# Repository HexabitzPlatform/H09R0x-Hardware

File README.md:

# H09R0x-Hardware
Hexabitz Thermocouple Sensor Module Hardware Design

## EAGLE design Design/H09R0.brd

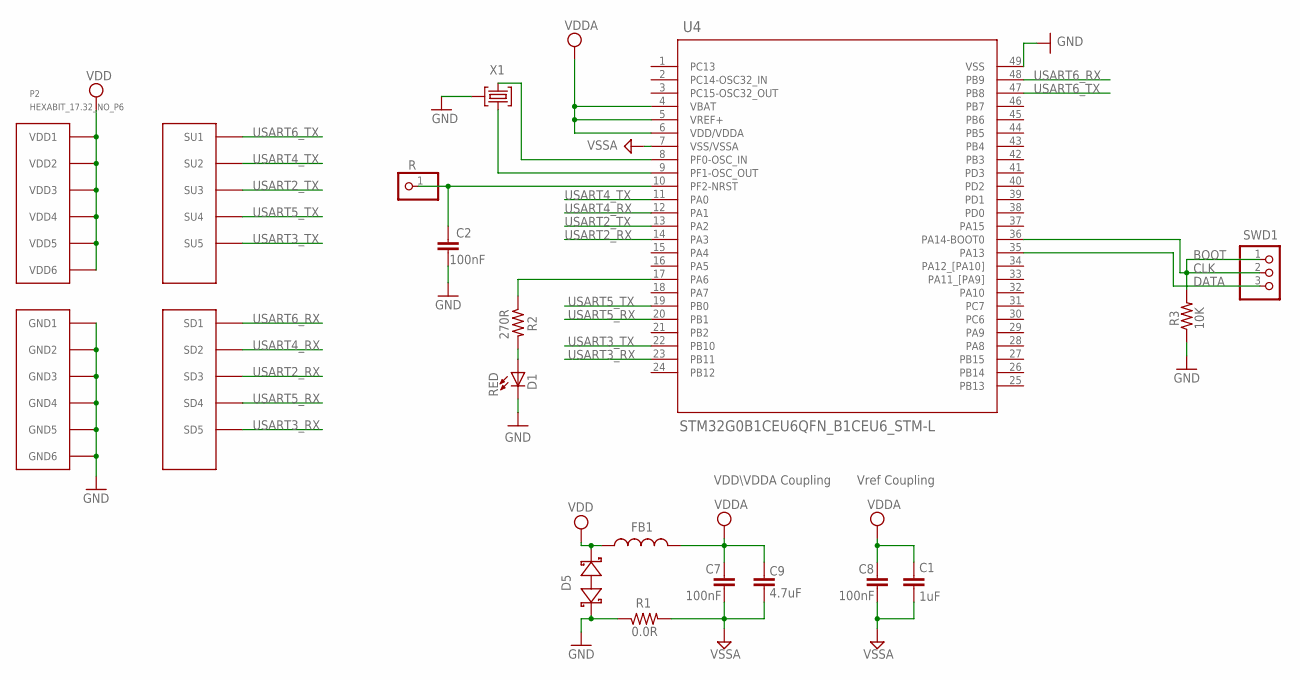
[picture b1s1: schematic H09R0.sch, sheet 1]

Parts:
C1: 1uF; C-0805
C2, C7, C8: 100nF; C-0603
C9: 4.7uF; C-0805
D1: RED; VLMS1300-GS08; MPN VLMS1300-GS08
D5: BOURNS_CDSOD323-T03SCBOURNS_CDSOD323-T03SC_0_0; BOURNS_CDSOD323-T03SC_0
FB1: FB-TDK_MMZ1608Y300B; FB-0603; MPN MMZ1608Y300B
P2: HEXABIT_17.32_NO_P6
R: R; 1X01
R1: 0.0R; R-0603; MPN RC0603JR-070RL
R2: 270R; R-0603
R3: 10K; R-0603
SWD1: PINHD-1X3; 1X03
U4: STM32G0B1CEU6QFN_B1CEU6_STM-L; QFN_B1CEU6_STM-L
X1: XTALL_CSTCE8M00G52

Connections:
CLK: R3.2, SWD1.1, SWD1.2, U4.36 (PA14-BOOT0)
DATA: SWD1.3, U4.35 (PA13)
GND: C2.2, D1.C, D5.1 (A), P2.PAD_PD7 (GND1), P2.PAD_PD8 (GND2), P2.PAD_PD9 (GND3), P2.PAD_PD10 (GND4), P2.PAD_PD11 (GND5), P2.PAD_PD12 (GND6), R1.1, R3.1, U4.49 (VSS), X1.P$2 (2); also elsewhere on the board
unnamed: U4.9 (PF1-OSC_OUT), X1.P$1 (1)
unnamed: U4.8 (PF0-OSC_IN), X1.P$3 (3)
unnamed: C2.1, R.1, U4.10 (PF2-NRST)
unnamed: R2.1, U4.17 (PA6)
unnamed: D1.A, R2.2
USART2_RX: P2.PAD_PD3 (SD3), U4.14 (PA3)
USART2_TX: P2.PAD_PU3 (SU3), U4.13 (PA2)
USART3_RX: P2.PAD_PD5 (SD5), U4.23 (PB11)
USART3_TX: P2.PAD_PU5 (SU5), U4.22 (PB10)
USART4_RX: P2.PAD_PD2 (SD2), U4.12 (PA1)
USART4_TX: P2.PAD_PU2 (SU2), U4.11 (PA0)
USART5_RX: P2.PAD_PD4 (SD4), U4.20 (PB1)
USART5_TX: P2.PAD_PU4 (SU4), U4.19 (PB0)
USART6_RX: P2.PAD_PD1 (SD1), U4.48 (PB9)
USART6_TX: P2.PAD_PU1 (SU1), U4.47 (PB8)
VDD: D5.2 (C), FB1.2, P2.PAD_PU7 (VDD1), P2.PAD_PU8 (VDD2), P2.PAD_PU9 (VDD3), P2.PAD_PU10 (VDD4), P2.PAD_PU11 (VDD5), P2.PAD_PU12 (VDD6); also elsewhere on the board
VDDA: C1.1, C7.1, C8.1, C9.1, FB1.1, U4.4 (VBAT), U4.5 (VREF+), U4.6 (VDD/VDDA)
VSSA: C1.2, C7.2, C8.2, C9.2, R1.2, U4.7 (VSS/VSSA)

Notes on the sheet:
Vref Coupling
VDD\VDDA Coupling
BOOT

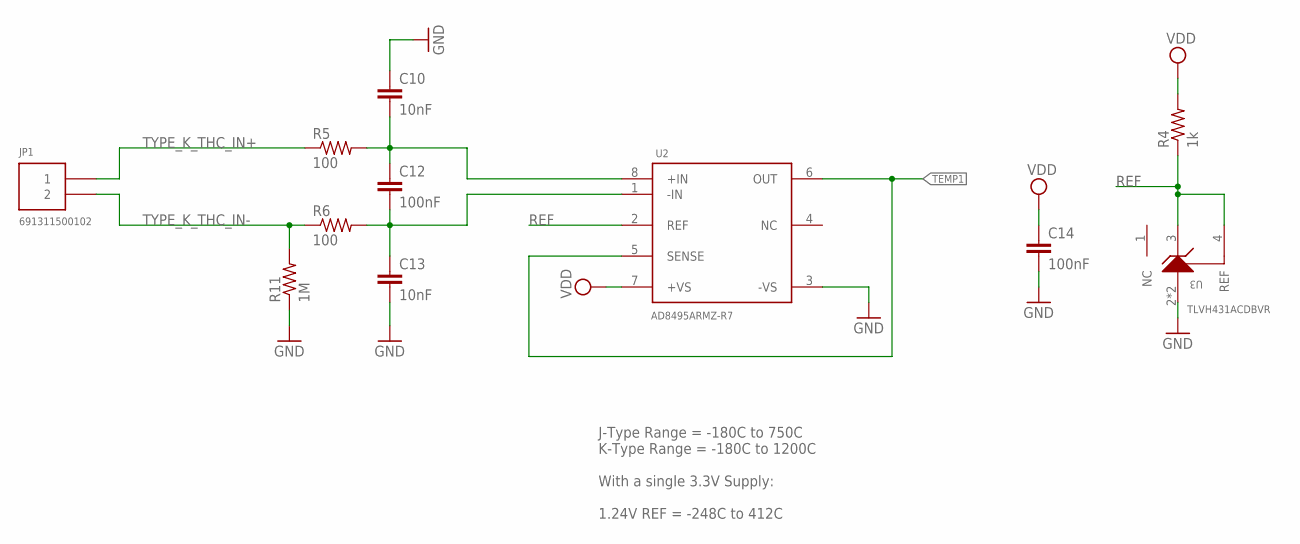
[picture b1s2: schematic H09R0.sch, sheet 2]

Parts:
C10, C13: 10nF; C-0603; TOLERANCE 10%; VOLTAGE_RATING 50V; MPN C0603C103K5RACTU
C12, C14: 100nF; C-0603; TOLERANCE 10%; VOLTAGE_RATING 10V; MPN C0603C104K8RACTU
JP1: 691311500102; 1546111-2
R4: 1k; R-0402; TOLERANCE 1%; MPN RC0402FR-071KL
R5, R6: 100; R-0402; TOLERANCE 1%; MPN RC0402FR-07100RL
R11: 1M; R-0402; TOLERANCE 1%; MPN RC0402FR-071ML
U2: AD8495ARMZ-R7; AD8495ARMZ
U3: TLVH431ACDBVR

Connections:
GND: C10.1, C13.2, C14.2, R11.1, U2.3 (-VS), U3.2 (ANODE), U3.5 (ANODE); also elsewhere on the board
unnamed: C10.2, C12.1, R5.2, U2.8 (+IN)
unnamed: C12.2, C13.1, R6.2, U2.1 (-IN)
REF: R4.1, U2.2 (REF), U3.3 (CATHODE), U3.4 (REF)
TEMP1: U2.5 (SENSE), U2.6 (OUT)
TYPE_K_THC_IN+: JP1.1, R5.1
TYPE_K_THC_IN-: JP1.2, R6.1, R11.2
VDD: C14.1, R4.2, U2.7 (+VS); also elsewhere on the board

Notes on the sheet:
J-Type Range = -180C to 750C K-Type Range = -180C to 1200C With a single 3.3V Supply: 1.24V REF = -248C to 412C

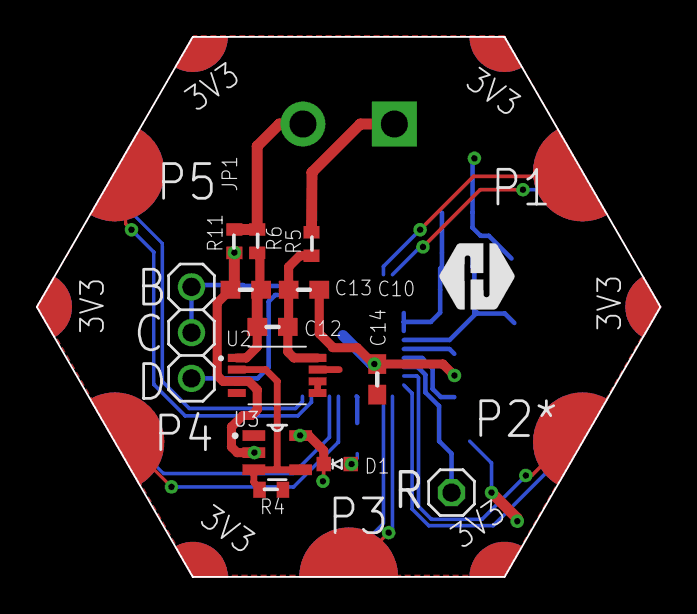
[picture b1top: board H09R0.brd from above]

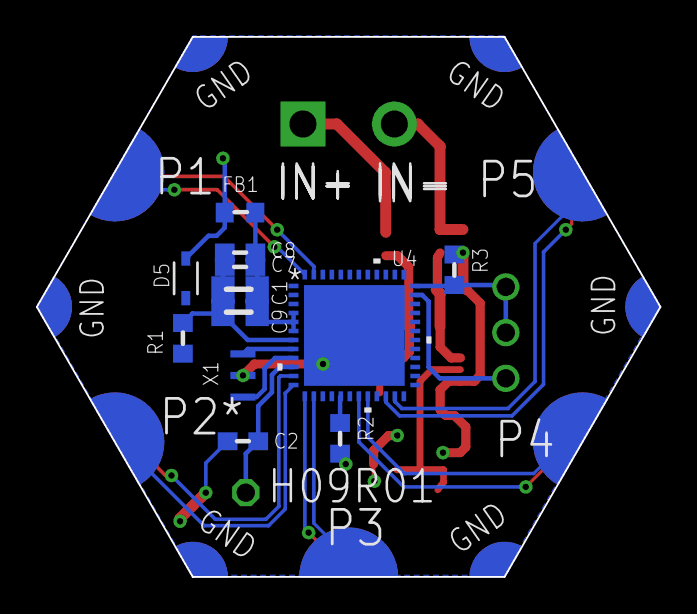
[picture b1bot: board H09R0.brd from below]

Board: 2 copper layers, 34.6 x 30.0 mm, 28 parts (12 on the bottom side), 27 nets.

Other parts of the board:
U$1: HEXA-LOGO

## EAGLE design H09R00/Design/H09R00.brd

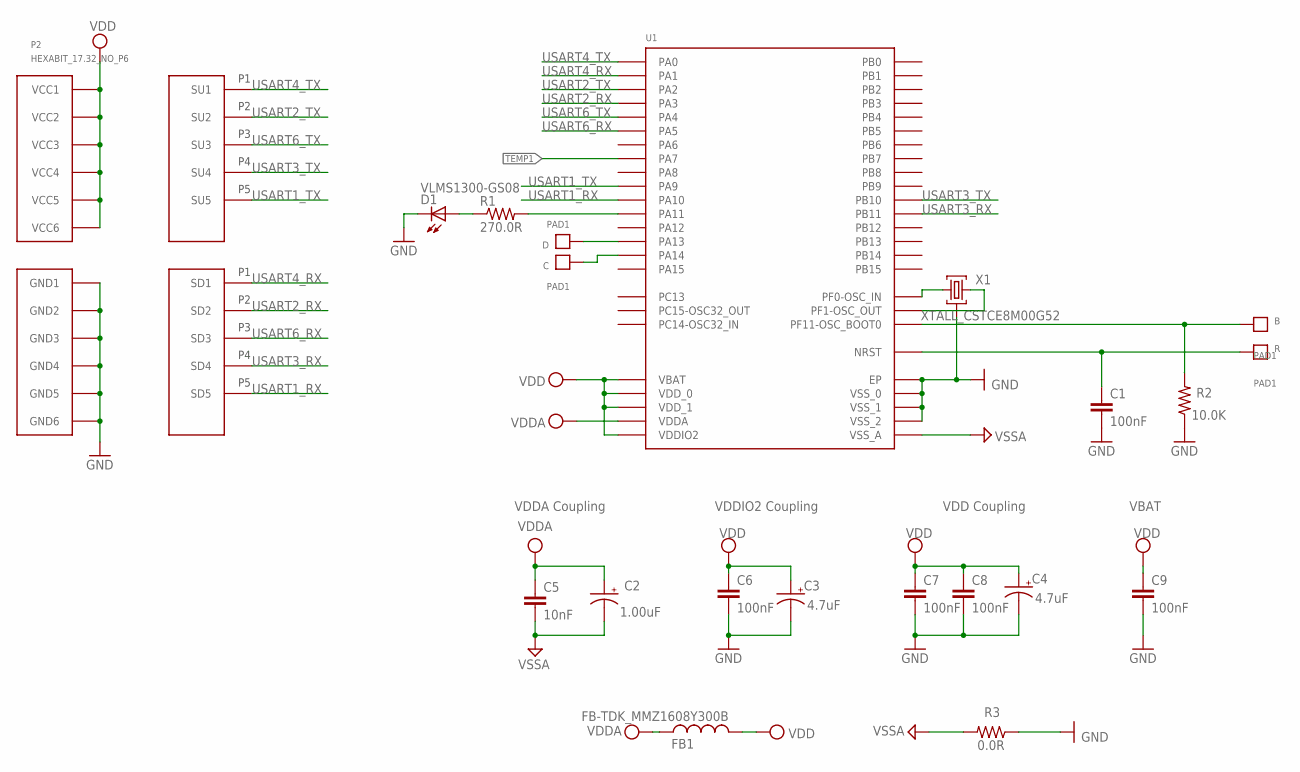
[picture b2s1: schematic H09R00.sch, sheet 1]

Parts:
B: PAD1
C: PAD1
C1, C6, C8: 100nF; C-0603; TOLERANCE 10%; VOLTAGE_RATING 10V; MPN C0603C104K8RACTU
C2: 1.00uF; C-0805-POL; TOLERANCE 10%; VOLTAGE_RATING 16V; MPN CC0805KKX7R7BB105
C3, C4: 4.7uF; C-0805-POL; TOLERANCE 10%; VOLTAGE_RATING 25V; MPN GRM21BC81E475KA12L
C5: 10nF; C-0603; TOLERANCE 10%; VOLTAGE_RATING 50V; MPN C0603C103K5RACTU
C7: 100nF; C-0603; TOLERANCE 10%; VOLTAGE_RATING 10; MPN C0603C104K8RACTU
C9: 100nF; C-0603; TOLERANCE 10V; VOLTAGE_RATING 10%; MPN C0603C104K8RACTU
D: PAD1
D1: VLMS1300-GS08; MPN VLMS1300-GS08
FB1: FB-TDK_MMZ1608Y300B; MPN MMZ1608Y300B
P2: HEXABIT_17.32_NO_P6
R: PAD1
R1: 270.0R; R-0603; TOLERANCE 1%; MPN RC0603FR-07270RL
R2: 10.0K; R-0603; TOLERANCE 5%; MPN RC0603JR-0710KL
R3: 0.0R; R-0603; MPN RC0603JR-070RL
U1: STM32F091CBU6
X1: XTALL_CSTCE8M00G52

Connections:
B: B.P$1, B.P$2, R2.2, U1.P$44 (PF11-OSC_BOOT0)
GND: C1.2, C3.2 (-), C4.2 (-), C6.2, C7.2, C8.2, C9.2, D1.C, P2.7 (GND1), P2.8 (GND2), P2.9 (GND3), P2.10 (GND4), P2.11 (GND5), P2.12 (GND6), R2.1, R3.1, U1.EP, U1.P$23 (VSS_0), U1.P$35 (VSS_1), U1.P$47 (VSS_2), X1.P$2 (2); also elsewhere on the board
unnamed: D.P$1, D.P$2, U1.P$34 (PA13)
unnamed: C.P$1, C.P$2, U1.P$37 (PA14)
unnamed: R1.2, U1.P$32 (PA11)
unnamed: D1.A, R1.1
unnamed: U1.P$5 (PF0-OSC_IN), X1.P$1 (1)
unnamed: U1.P$6 (PF1-OSC_OUT), X1.P$3 (3)
R: C1.1, R.P$1, R.P$2, U1.P$7 (NRST)
TEMP1: U1.P$17 (PA7); also elsewhere on the board
USART1_RX: P2.23 (SD5), U1.P$31 (PA10)
USART1_TX: P2.17 (SU5), U1.P$30 (PA9)
USART2_RX: P2.20 (SD2), U1.P$13 (PA3)
USART2_TX: P2.14 (SU2), U1.P$12 (PA2)
USART3_RX: P2.22 (SD4), U1.P$22 (PB11)
USART3_TX: P2.16 (SU4), U1.P$21 (PB10)
USART4_RX: P2.19 (SD1), U1.P$11 (PA1)
USART4_TX: P2.13 (SU1), U1.P$10 (PA0)
USART6_RX: P2.21 (SD3), U1.P$15 (PA5)
USART6_TX: P2.15 (SU3), U1.P$14 (PA4)
VDD: C3.1 (+), C4.1 (+), C6.1, C7.1, C8.1, C9.1, FB1.2, P2.1 (VCC1), P2.2 (VCC2), P2.3 (VCC3), P2.4 (VCC4), P2.5 (VCC5), P2.6 (VCC6), U1.P$1 (VBAT), U1.P$24 (VDD_0), U1.P$36 (VDDIO2), U1.P$48 (VDD_1); also elsewhere on the board
VDDA: C2.1 (+), C5.1, FB1.1, U1.P$9 (VDDA)
VSSA: C2.2 (-), C5.2, R3.2, U1.P$8 (VSS_A)

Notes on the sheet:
VDDA Coupling
VDDIO2 Coupling
VDD Coupling
VBAT

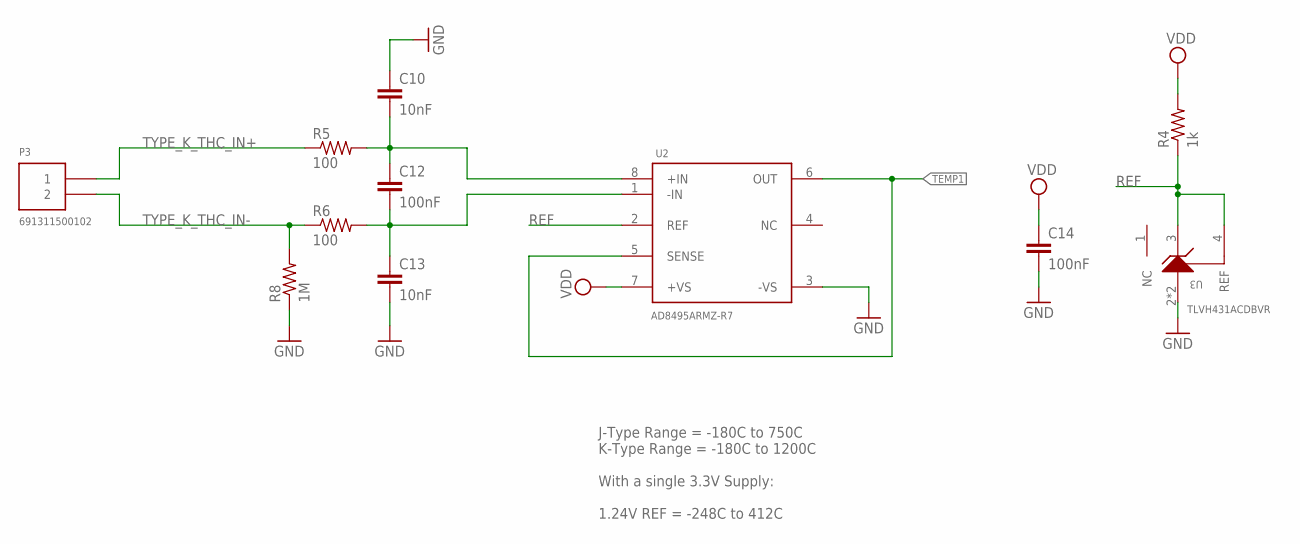
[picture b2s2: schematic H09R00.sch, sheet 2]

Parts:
C10, C13: 10nF; C-0603; TOLERANCE 10%; VOLTAGE_RATING 50V; MPN C0603C103K5RACTU
C12, C14: 100nF; C-0603; TOLERANCE 10%; VOLTAGE_RATING 10V; MPN C0603C104K8RACTU
P3: 691311500102
R4: 1k; R-0402; TOLERANCE 1%; MPN RC0402FR-071KL
R5, R6: 100; R-0402; TOLERANCE 1%; MPN RC0402FR-07100RL
R8: 1M; R-0402; TOLERANCE 1%; MPN RC0402FR-071ML
U2: AD8495ARMZ-R7; AD8495ARMZ
U3: TLVH431ACDBVR

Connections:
GND: C10.1, C13.2, C14.2, R8.1, U2.3 (-VS), U3.2 (ANODE), U3.5 (ANODE); also elsewhere on the board
unnamed: C10.2, C12.1, R5.2, U2.8 (+IN)
unnamed: C12.2, C13.1, R6.2, U2.1 (-IN)
REF: R4.1, U2.2 (REF), U3.3 (CATHODE), U3.4 (REF)
TEMP1: U2.5 (SENSE), U2.6 (OUT); also elsewhere on the board
TYPE_K_THC_IN+: P3.1, R5.1
TYPE_K_THC_IN-: P3.2, R6.1, R8.2
VDD: C14.1, R4.2, U2.7 (+VS); also elsewhere on the board

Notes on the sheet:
J-Type Range = -180C to 750C K-Type Range = -180C to 1200C With a single 3.3V Supply: 1.24V REF = -248C to 412C

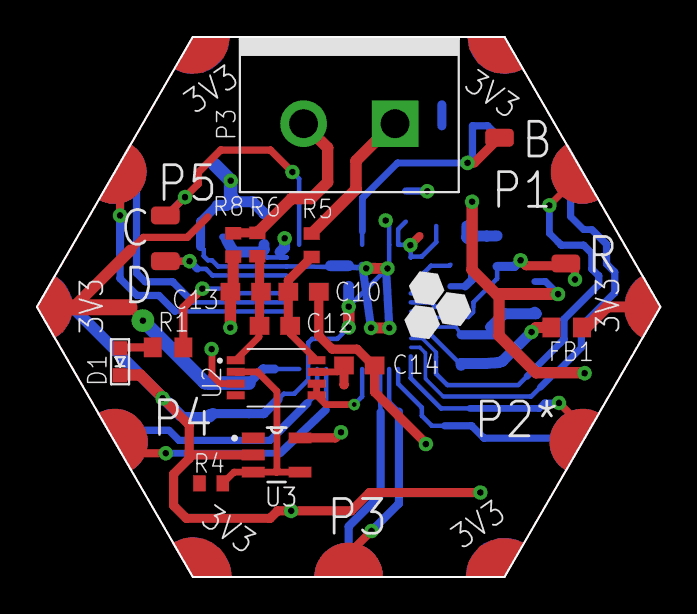
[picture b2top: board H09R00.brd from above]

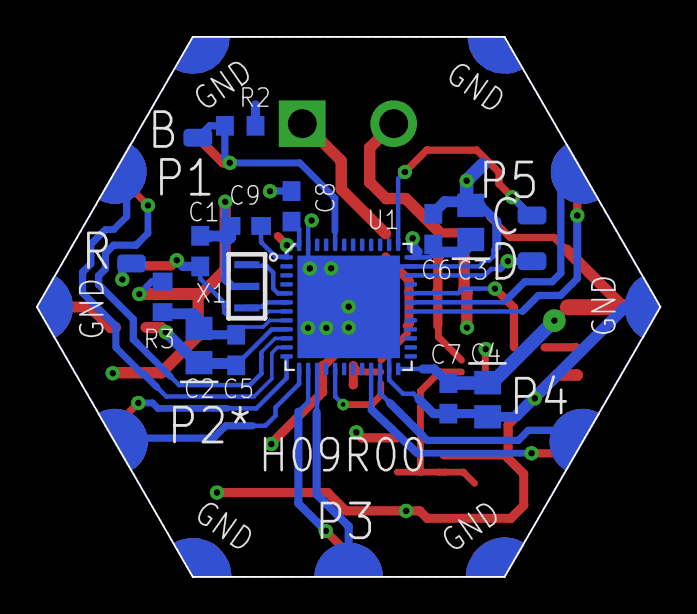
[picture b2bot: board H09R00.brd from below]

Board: 2 copper layers, 34.6 x 30.0 mm, 32 parts (13 on the bottom side), 28 nets.

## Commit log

2019-05-23 First release rev 0
2019-08-13 Fix schematics PDF colors
2024-01-02 -Standarize the files and folders
2024-12-12 - Deleted old output files - Changed MCU to G0 - New schematic - New layout - Generated documentation - Generated BOM
2024-12-14 - Deleted yellow and orange LEDs from design - Changed connector - Changed RESs and CAPs and used from our library - New layout - Changed polygon to thermal - Rearranged compenents in BOM
2024-12-14 - Rearranged components in BOM
2024-12-14 - Changed logo in layout - Rearranged components in BOM

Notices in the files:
parts and their libraries:
COPYRIGHT: Copyright (C) 2021 Ultra Librarian. All rights reserved.
